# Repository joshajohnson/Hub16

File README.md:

# Hub16

Hub16 is a macropad with a bunch of features you never knew you needed. They include:

- 16 Cherry MX compatible keys, along with switches in each encoder.
- Two rotary encoders, enabling intuitive controls for a wide range of tools including CAD and photo / video editing.
- Inbuilt USB 2.0 Hub with Type-C connectors, allowing connection to other keyboards, memory sticks, wireless receivers and more!
- VIA and QMK compatibility, including a "macro" mode enabling the keys to be dynamically remapped on a host computer.
- 11 addressable RGB LEDs to display state, or just light your desk up.

## Project Status

Project is stable, with assembled boards available at [Tindie](https://www.tindie.com/products/joshajohnson/hub16-programmable-macro-keyboard/).

## Getting Started Guide

- [Keyboard Assembly](Documents/keyboard-assembly.md)
- [VIA Keymap Configuration](Documents/via.md)
- [Macro Configuration](Documents/macro.md)

## Detailed Info

- [Advanced Firmware / Software Configuration](Documents/advanced-config.md)
- [PCB SMT Assembly Guide](Documents/pcba.md)
- [Enclosure Manufacturing](Documents/enclosure.md)

### Repo Contents

- `Documents` contains all documentation and images for the project.
- `Firmware` contains both the source and precompiled binaries for Hub16.
- `Hardware` contains the KiCad design files for the keyboard.
- `josh-kicad-lib` is my personal KiCad parts library which contains many of the parts used.
- `Mechanicals` contain the plate and case design for Hub16.
- `Production` contains all the files required to produce the PCB. It also contains test scripts and jigs.
- `Software` contains all the VIA config, along with template script to use Hub16 as a macropad with software on your computer.

### Notes on the USB Hub

The hub is a four port USB 2.0 Hub with Type-C connectors, aimed at allowing connection of keyboards, mice, memory sticks, wireless receivers, and other small devices (including a second Hub16!)  to your computer.

Due to cost and space constraints, the hub has some limitations. The hub **is not**:

- USB 3.x, Power Delivery, Thunderbolt, DisplayPort, etc compatible.
- Designed to charge your phone quickly. Only 100mA is guaranteed per port.
- Designed to work with power hungry devices such as spinning hard drives.
- Guaranteed to provide full USB 2.0 speeds and performance on all ports.

Might you be able to charge your phone whilst copying files at full speed of a spinning hard drive over a long cable? Maybe. However Hub16 is a macropad first, USB hub second, so if you are looking for a high performance device I'd suggest picking up a dedicated USB hub and just using Hub16 as a macropad.

### Errata

- Boards assembled in 2021 will have an issue with VIA where the LED controls are incorrect. [Follow these instructions to resolve](Documents/via.md#install-via)
- Boards purchased between June 12 and June 22 2020 will not go into the bootloader upon resting from software. Workaround: reset board with physical reset button on bottom of PCB. Fix: reflash the bootloader following [these instructions](Documents/advanced-config.md#Bootloader-Flashing).
- Firmware builds prior to 27th June do not continually send characters when the encoders are depressed.
- Firmware builds prior to 9th June have issues with the bottom right key `p` not functioning correctly.
- Some rotary encoders output flipped signals (clockwise instead of counterclockwise), if after assembly your encoders appear to be sending the wrong signals, comment in line 84 in [config.h](Firmware/hub16/config.h), or alter the setting in your [software](Software).

If you have any questions or comments please get in touch. Asking in the [No Sharp Corners Discord](nosharpcorners.com) Discord or opening an issue / pull request will result in the quickest response.

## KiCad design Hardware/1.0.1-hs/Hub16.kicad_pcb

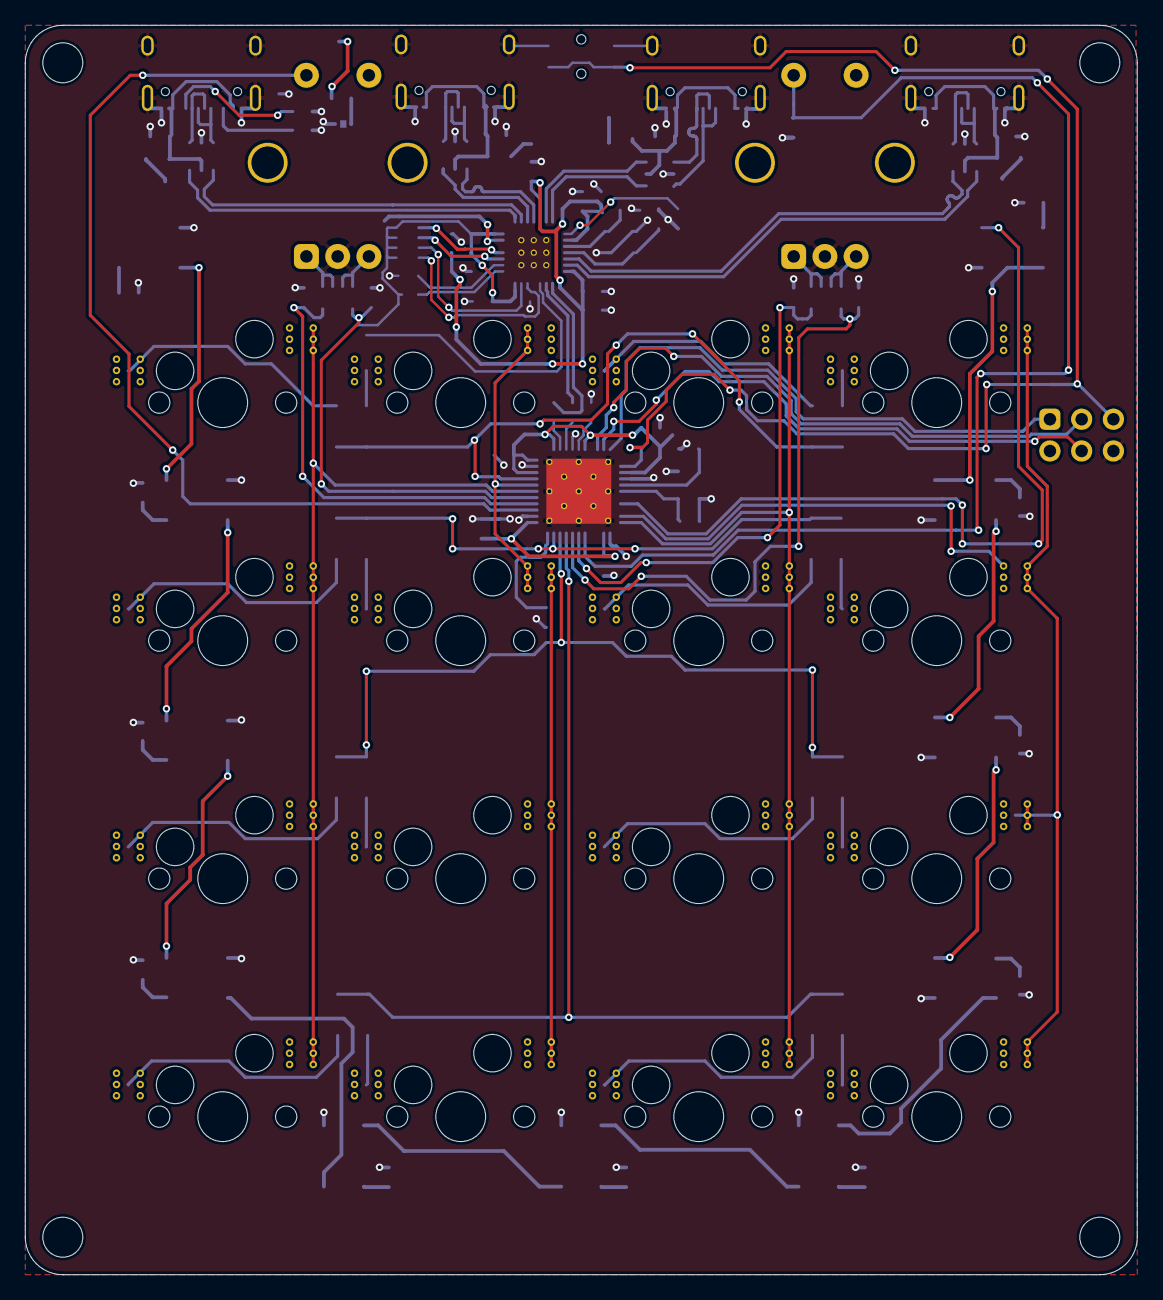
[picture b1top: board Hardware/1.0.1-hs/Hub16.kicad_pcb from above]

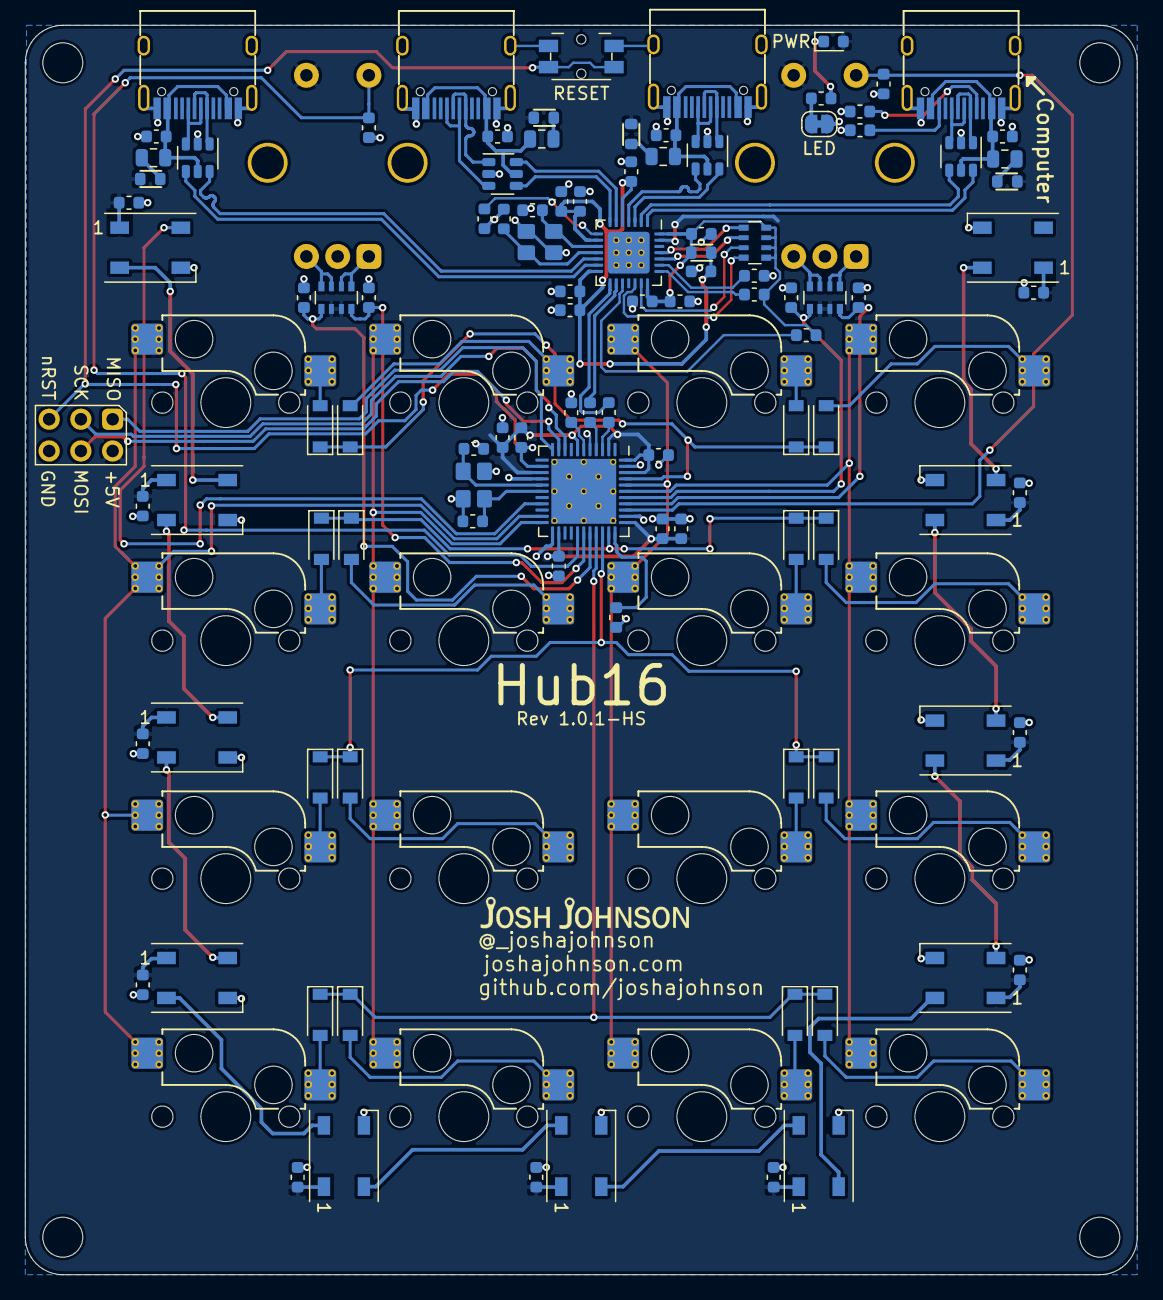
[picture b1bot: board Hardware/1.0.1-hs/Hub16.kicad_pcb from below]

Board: 2 copper layers, 89.0 x 100.0 mm, 132 parts (126 on the bottom side), 99 nets.

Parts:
C1, C12: 10u; C_0603_1608Metric
C2, C3, C17, C18: 15p; C_0603_1608Metric
C4, C5, C19, C20, C22: 1u; C_0603_1608Metric
C6, C7, C8, C9, C10, C11, C13, C14, C15, C16, C21, C23, C24, C25, C26, C27, C28, C29, C30, C31, C32, C33, C34, C35, C36, C37, C38: 100n; C_0603_1608Metric
D1: LED; LED_0603_1608Metric
D2, D3, D4, D10, D16, D22, D23, D29, D30, D31, D32: WS2812B; LED_WS2812B_PLCC4_5.0x5.0mm_P3.2mm
D5, D6, D7, D8, D11, D12, D13, D14, D17, D18, D19, D20, D24, D25, D26, D27: 1N4148; D_SOD-123
F1: 1A; Fuse_0805_2012Metric
F2, F3, F4: 500mA; Fuse_0805_2012Metric
FB1, FB2, FB3, FB4, FB5: 600R; Ferrite_Bead_0603
H1, H2, H3, H4: MH-M3; MountingHole_3.2mm_M3_ISO14580
J1, J3, J4, J5: USB_C_Receptacle_USB2.0; USB_C_U262-161N-4BVC11
J2: AVR-ISP-6; AVR_PROG_2.54_THT
JP11: LED_ON; SolderJumper-2_P1.3mm_Bridged_RoundedPad1.0x1.5mm
K1, K2, K3, K4, K6, K7, K8, K9, K11, K12, K13, K14, K16, K17, K18, K19: Kailh Hotswap Socket; Kailh_Hotswap_1U
LOGO1: Josh-Logo; josh-johnson-logo-17x3
LOGO2: Josh-Details; josh-details
LOGO3: Board-Details; board-title
LOGO4: Logo_Open_Hardware_Small; OSHW-Logo2_9.8x8mm_Mask
R1, R3, R4: 5K1; R_0603_1608Metric
R2, R5, R8, R9, R10, R11, R12: 10K; R_0603_1608Metric
R6, R7: 22R; R_0603_1608Metric
R14: 649R; R_0603_1608Metric
RN1, RN3, RN5: 10K; R_Array_Convex_4x0603
SW1: EVQPUL; Panasonic_EVQPUL_EVQPUC
SW2, SW3: EC11 Encoder; RotaryEncoder_Alps_EC11E-Switch_Vertical_H20mm_CircularMoun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
U1, U4, U5, U6: USBLC6-2SC6; SOT-23-6
U2: ATMEGA32U4; QFN-44-1EP_7x7mm_P0.5mm_EP5.2x5.2mm_ThermalVias
U3: CY7C65632-28LTXCT; QFN-28-1EP_5x5mm_P0.5mm_EP3.35x3.35mm_ThermalVias
Y1: 16MHz; Crystal_SMD_3225-4Pin_3.2x2.5mm
Y2: 12MHz; Crystal_SMD_3225-4Pin_3.2x2.5mm

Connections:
+3.3VA: C13.1, C14.1, C15.1, C16.1, C19.1, C20.1, FB1.1, U3.5, U3.9, U3.14
+3V3: C12.1, C21.1, C22.1, FB1.2, R10.2, R12.2, RN5.5, RN5.6, RN5.7, RN5.8, U3.21, U3.28
+5V: C5.1, C6.2, C7.2, C23.1, C27.1, C28.1, C29.1, C30.1, C31.1, C32.1, C33.1, C34.1, C35.1, C36.1, C37.1, C38.2, D1.2, D2.1, D3.1, D4.1, D10.1, D16.1, D22.1, D23.1, D29.1, D30.1, D31.1, D32.1, FB2.2, FB3.2, FB4.2, FB5.2, J2.2, R2.1, RN1.2, RN1.3, RN3.2, RN3.3, SW2.S1, SW3.S1, U2.2, U2.7, U2.14, U2.24, U2.34, U2.42, U2.44, U3.27
/ENC_1_A: C9.1, RN3.4, U2.37
/ENC_1_B: C8.1, RN3.1, U2.38
/ENC_1_SW: R8.2, SW2.S2, U2.36
/ENC_2_A: C11.1, RN1.4, U2.28
/ENC_2_B: C10.1, RN1.1, U2.29
/ENC_2_SW: R11.2, SW3.S2, U2.27
/LED_1: D22.2, D23.4
/LED_DAT: D2.4, U2.19
/MISO: J2.1, U2.11
/MOSI: J2.4, U2.10
/SCK: J2.3, U2.9
/USB Hub/CON2_D+: J3.A6, J3.B6, U6.3
/USB Hub/CON2_D-: J3.A7, J3.B7, U6.1
/USB Hub/D1_D+: U3.4, U5.4
/USB Hub/D1_D-: U3.3, U5.6
/USB Hub/D2_D+: U3.7, U6.4
/USB Hub/D2_D-: U3.6, U6.6
/USB Hub/D3_D+: U3.13, U4.4
/USB Hub/D3_D-: U3.12, U4.6
/USB Hub/UP_USB_N: U1.6, U3.1
/USB Hub/UP_USB_P: U1.4, U3.2
/USB Hub/USB_DN_D+: R6.2, U3.16
/USB Hub/USB_DN_D-: R7.2, U3.15
/USB Hub/XIN: C17.1, U3.10, Y2.1
/USB Hub/XOUT: C18.1, U3.11, Y2.3
/USB Hub/nOVR_1: RN5.1, U3.25
/USB Hub/nOVR_2: RN5.2, U3.24
/USB Hub/nOVR_3: RN5.3, U3.20
/USB Hub/nOVR_4: RN5.4, U3.19
/USB_UP_D+: J1.A6, J1.B6, U1.3
/USB_UP_D-: J1.A7, J1.B7, U1.1
/col1: K1.1, K2.1, K3.1, K4.1, U2.39
/col2: K6.1, K7.1, K8.1, K9.1, U2.40
/col3: K11.1, K12.1, K13.1, K14.1, U2.22
/col4: K16.1, K17.1, K18.1, K19.1, U2.21
/nRST: J2.5, R2.2, SW1.2, U2.13
/row1: D5.1, D11.1, D17.1, D24.1, U2.41
/row2: D6.1, D12.1, D18.1, D25.1, U2.32
/row3: D7.1, D13.1, D19.1, D26.1, U2.31
/row4: D8.1, D14.1, D20.1, D27.1, U2.30
GND: C1.2, C2.2, C3.2, C4.2, C5.2, C6.1, C7.1, C8.2, C9.2, C10.2, C11.2, C12.2, C13.2, C14.2, C15.2, C16.2, C17.2, C18.2, C19.2, C20.2, C21.2, C22.2, C23.2, C24.2, C25.2, C26.2, C27.2, C28.2, C29.2, C30.2, C31.2, C32.2, C33.2, C34.2, C35.2, C36.2, C37.2, C38.1, D2.3, D3.3, D4.3, D10.3, D16.3, D22.3, D23.3, D29.3, D30.3, D31.3, D32.3, J1.A1, J1.A12, J1.B1, J1.B12, J1.S1, J2.6, J3.A1, J3.A12, J3.B1, J3.B12, J3.S1, J4.A1, J4.A12, J4.B1, J4.B12, J4.S1, J5.A1, J5.A12, J5.B1, J5.B12, J5.S1, JP11.2, R3.1, R4.1, R5.2, R8.1, R9.2, R11.1, R14.2, SW1.1, SW2.C, SW3.C, U1.2, U2.5, U2.15, U2.23, U2.35, U2.43, U2.45, U3.29, U4.2, U5.2, U6.2, Y1.2, Y1.4, Y2.2, Y2.4
unnamed: C2.1, U2.16, Y1.1
unnamed: C3.1, U2.17, Y1.3
unnamed: C4.1, U2.6
unnamed: C24.1, F2.1, J5.A4, J5.A9, J5.B4, J5.B9, U4.5
unnamed: C25.1, F3.1, J4.A4, J4.A9, J4.B4, J4.B9, U5.5
unnamed: C26.1, F4.1, J3.A4, J3.A9, J3.B4, J3.B9, U6.5
unnamed: D1.1, R1.1
unnamed: D2.2, D3.4
unnamed: D3.2, D4.4
unnamed: D5.2, K1.2
unnamed: D6.2, K2.2
unnamed: D7.2, K3.2
unnamed: D8.2, K4.2
unnamed: D10.2, D16.4
unnamed: D4.2, D10.4
unnamed: D11.2, K6.2
unnamed: D12.2, K7.2
unnamed: D13.2, K8.2
unnamed: D14.2, K9.2
unnamed: D16.2, D22.4
unnamed: D17.2, K11.2
unnamed: D18.2, K12.2
unnamed: D19.2, K13.2
unnamed: D20.2, K14.2
unnamed: D23.2, D29.4
unnamed: D24.2, K16.2
unnamed: D25.2, K17.2
unnamed: D26.2, K18.2
unnamed: D27.2, K19.2
unnamed: D29.2, D30.4
unnamed: D30.2, D31.4
unnamed: D31.2, D32.4
unnamed: F1.1, FB5.1
unnamed: F2.2, FB3.1
unnamed: F3.2, FB4.1
unnamed: F4.2, FB2.1
unnamed: J1.A5, R3.2
unnamed: J1.B5, R4.2
unnamed: J4.A6, J4.B6, U5.3
unnamed: J4.A7, J4.B7, U5.1
unnamed: J5.A6, J5.B6, U4.3
unnamed: J5.A7, J5.B7, U4.1
unnamed: JP11.1, R1.2
unnamed: R5.1, U2.33
unnamed: R6.1, U2.4
unnamed: R7.1, U2.3
unnamed: R9.1, U3.23
unnamed: R10.1, U3.17
unnamed: R12.1, U3.22
unnamed: R14.1, U3.8
unnamed: RN1.5, RN1.6, SW3.A
unnamed: RN1.7, RN1.8, SW3.B
unnamed: RN3.5, RN3.6, SW2.A
unnamed: RN3.7, RN3.8, SW2.B
VBUS: C1.1, F1.2, J1.A4, J1.A9, J1.B4, J1.B9, U1.5

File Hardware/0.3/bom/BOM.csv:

Unique ID,Qty,Reference(s),Value,Footprint,Digikey PN,LCSC PN,MPN,Substitute allowed,Notes
Hub16-1,12,"C1, C6, C7, C8, C9, C10, C11, C13, C14, C15, C16, C21",100n,Capacitor_SMD:C_0603_1608Metric,1276-1000-1-ND,,CL10B104KB8NNNC,Y,
Hub16-2,4,"C2, C3, C17, C18",22p,Capacitor_SMD:C_0603_1608Metric,1276-2228-1-ND  ,,CL10C220JB8NFNC ,Y,
Hub16-3,5,"C4, C5, C19, C20, C22",1u,Capacitor_SMD:C_0603_1608Metric,1276-1866-1-ND ,,CL10A105MP8NNNC ,Y,
Hub16-4,1,C12,10u,Capacitor_SMD:C_0603_1608Metric,1276-1871-1-ND ,,CL10A106MP8NNNC ,Y,
Hub16-5,1,D1,LED,LED_SMD:LED_0603_1608Metric,732-4980-1-ND  ,,150060VS75000,Y,
Hub16-6,11,"D2, D3, D4, D10, D16, D22, D23, D29, D30, D31, D32",WS2812B,keyboard:LED_WS2812B_PLCC4_5.0x5.0mm_P3.2mm,1528-1104-ND,C114586,WS2812B,N,LCSC PN - Black Model
Hub16-7,16,"D5, D6, D7, D8, D11, D12, D13, D14, D17, D18, D19, D20, D24, D25, D26, D27",D,Diode_SMD:D_SOD-123,1N4148W-FDICT-ND,C83528,1N4148W-7-F,Y,
Hub16-8,1,F1,500mA,keyboard:Fuse_0805_2012Metric,507-1813-1-ND,C181350,0ZCK0050FF2E,Y,LCSC: Substitute PN
Hub16-9,4,"FB1, FB2, FB3, FB4",600R,josh-passives-smt:Ferrite_Bead_0603,490-1014-1-ND,C19330,BLM18AG601SN1D,Y,
Hub16-10,4,"J1, J3, J4, J5",USB_C_Receptacle_USB2.0,josh-connectors:USB_C_Receptacle_GT-USB-7010,,C319148,U262-161N-4BVC11,N,"Cannot source from Digikey, available on AliExpress: https://www.aliexpress.com/item/33045191307.html"
Hub16-11,1,R1,2K2,Resistor_SMD:R_0603_1608Metric,CR0603-JW-222ELFCT-ND  ,,CR0603-JW-222ELF ,Y,
Hub16-12,5,"R2, R5, R8, R11, R12",10K,Resistor_SMD:R_0603_1608Metric,CR0603-JW-103ELFCT-ND  ,,CR0603-JW-103ELF ,Y,
Hub16-13,2,"R3, R4",5K1,Resistor_SMD:R_0603_1608Metric,118-CR0603-JW-512ELFCT-ND ,,CR0603-JW-512ELF ,Y,
Hub16-14,2,"R6, R7",22R,Resistor_SMD:R_0603_1608Metric,CR0603-JW-220ELFCT-ND  ,,CR0603-JW-220ELF ,Y,
Hub16-15,3,"R9, R10, R13",100K,Resistor_SMD:R_0603_1608Metric,CR0603-JW-104ELFCT-ND ,,CR0603-JW-104ELF ,Y,
Hub16-16,1,R14,649R,Resistor_SMD:R_0603_1608Metric,RHM649CFCT-ND  ,,MCR03ERTF6490 ,Y,
Hub16-17,3,"RN1, RN3, RN5",10K,Resistor_SMD:R_Array_Convex_4x0402,RAVF104DJT10K0CT-ND,,RAVF104DJT10K0,Y,
Hub16-18,1,SW1,SW_Push,josh-buttons-switches:BT_Small_2_Pin,401-1704-1-ND,C354946,KSR223GLFG,Y,LCSC: Substitute PN
Hub16-19,2,"SW2, SW3",Rotary_Encoder_Switch,keyboard:RotaryEncoder_Alps_EC11E-Switch_Vertical_H20mm_CircularMountingHoles,987-1398-ND,C361165,EC11E1834403,Y,Digikey: Substitute PN
Hub16-20,1,U1,TPD2S017,Package_TO_SOT_SMD:SOT-23-6,296-25216-1-ND ,,TPD2S017DBVR,N,"Cannot source from LCSC, no substitutes available "
Hub16-21,1,U2,ATMEGA32U4,Package_QFP:TQFP-44_10x10mm_P0.8mm,ATMEGA32U4-AURCT-ND,C44854,ATMEGA32U4-AU,N,
Hub16-22,1,U3,CY7C65632-28LTXCT,Package_DFN_QFN:QFN-28-1EP_5x5mm_P0.5mm_EP3.35x3.35mm_ThermalVias,428-3156-1-ND,C466886,CY7C65632-28LTXCT,N,
Hub16-23,1,Y1,16MHz,Crystal:Crystal_SMD_3225-4Pin_3.2x2.5mm,535-9134-1-ND ,C179641,ABM8-16.000MHZ-B2-T,Y,
Hub16-24,1,Y2,12MHz,Crystal:Crystal_SMD_3225-4Pin_3.2x2.5mm,535-9826-1-ND,C276421,ABM8-12.000MHZ-B2-T,Y,

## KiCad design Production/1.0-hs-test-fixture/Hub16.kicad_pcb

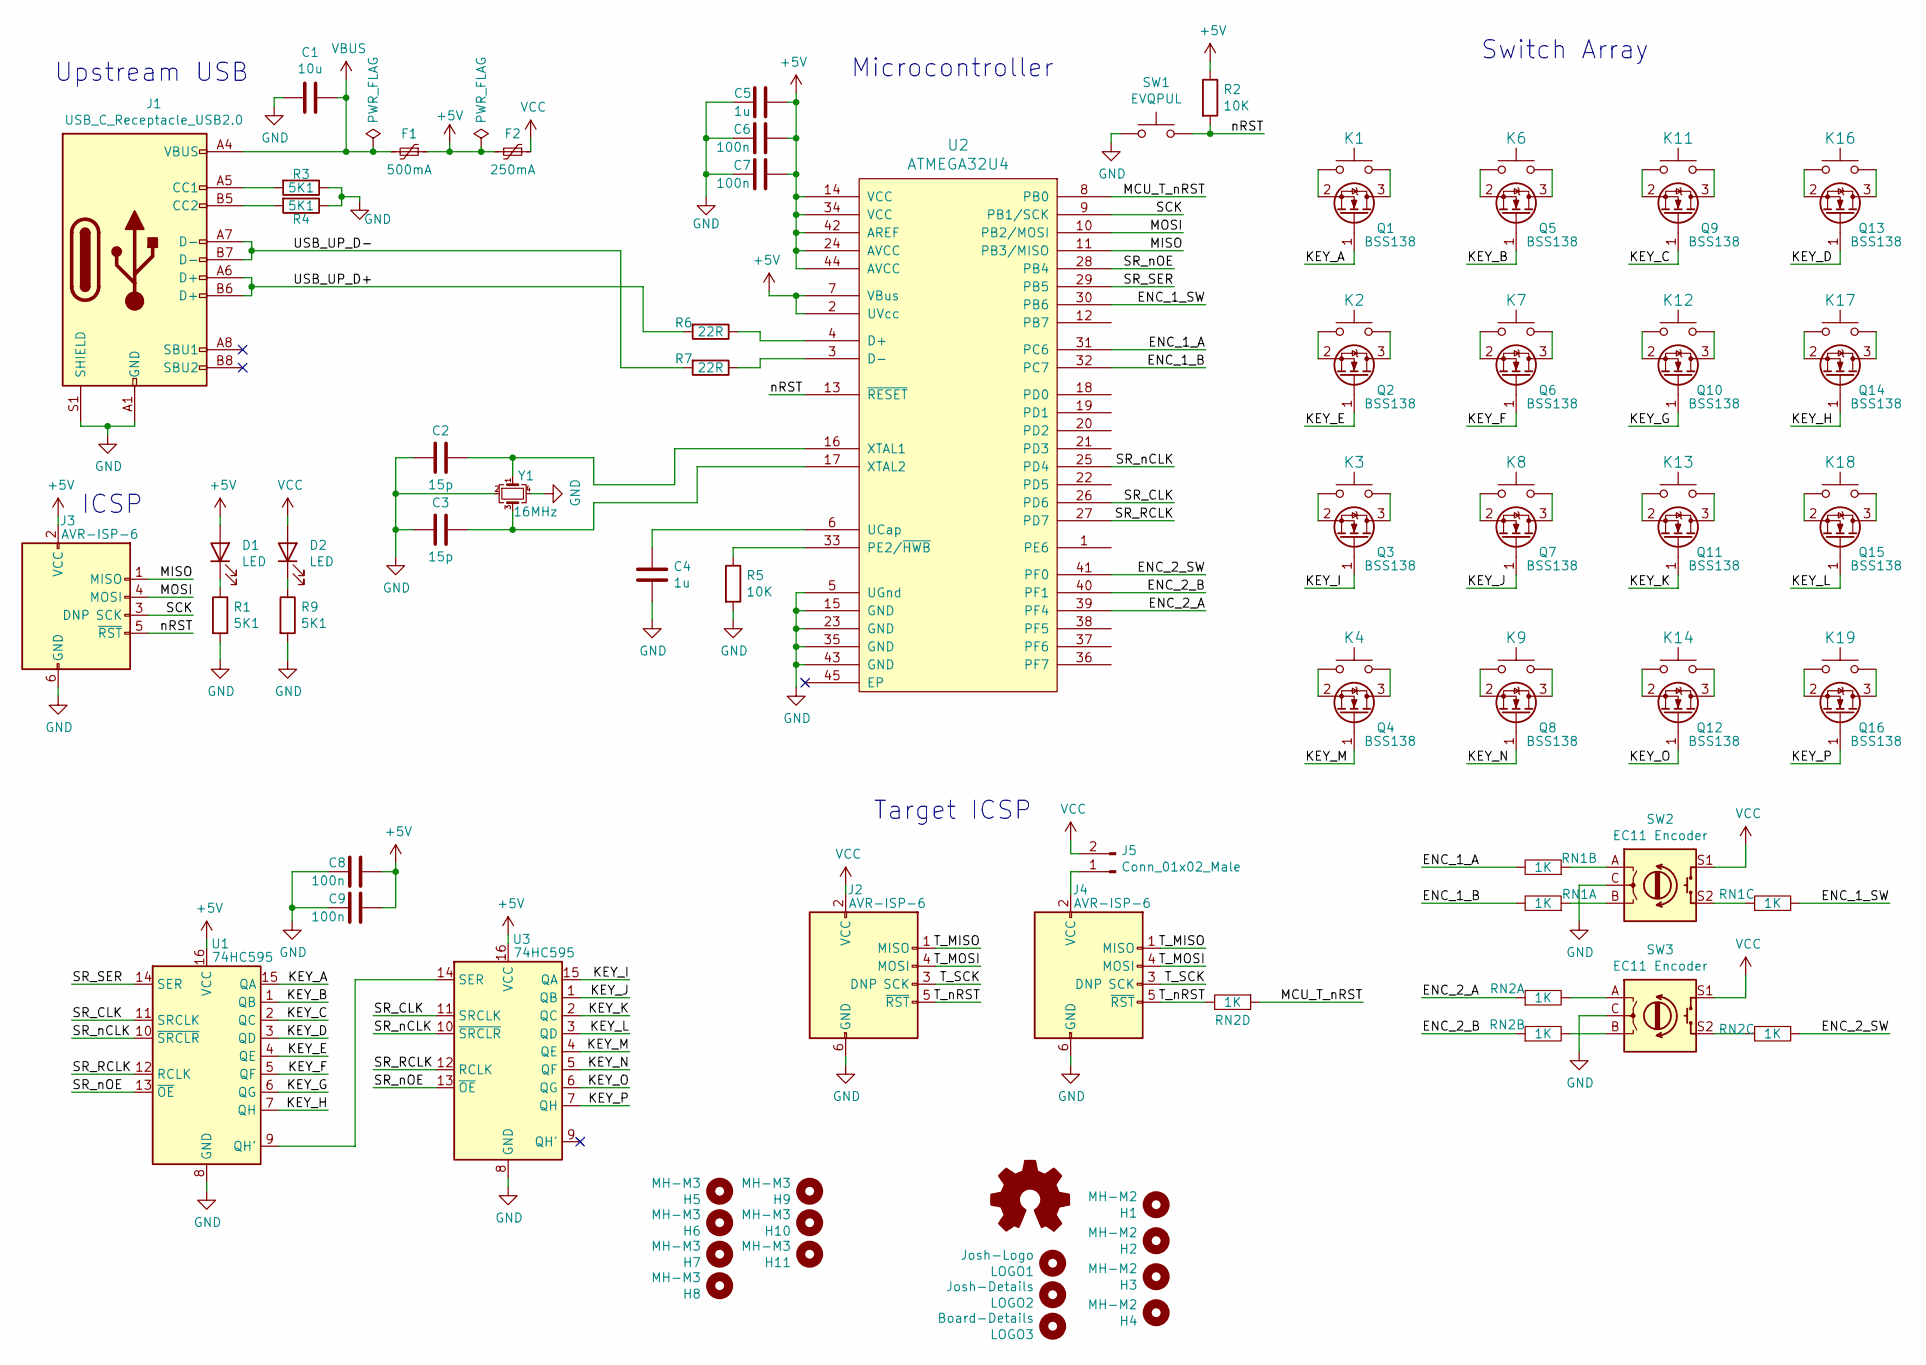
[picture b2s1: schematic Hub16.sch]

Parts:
C1: 10u; C_0603_1608Metric; MPN CL10A106MP8NNNC; DigiKey 1276-1871-1-ND
C2, C3: 15p; C_0603_1608Metric; MPN CL10C150JB8NNNC; DigiKey 1276-1296-2-ND
C4, C5: 1u; C_0603_1608Metric; MPN CL10A105MP8NNNC; DigiKey 1276-1866-1-ND
C6, C7, C8, C9: 100n; C_0603_1608Metric; MPN CL10B104KB8NNNC; DigiKey 1276-1000-1-ND
D1, D2: LED; LED_0603_1608Metric; MPN OSK40603C1E; LCSC C268294
F1: 500mA; Fuse_0805_2012Metric
F2: 250mA; Fuse_0805_2012Metric
H1, H2, H3, H4: MH-M2; MountingHole_2.2mm_M2
H5, H6, H7, H8, H9, H10, H11: MH-M3; MountingHole_3.2mm_M3_Pad
J1: USB_C_Receptacle_USB2.0; USB_C_U262-161N-4BVC11; MPN U262-161N-4BVC11; LCSC C319148
J2: AVR-ISP-6; POGO_P100_AVR_PROG_2.54_THT
J3: AVR-ISP-6; AVR_PROG_2.54_SMT
J4: AVR-ISP-6; IDC-Header_2x03_P2.54mm_Horizontal
J5: Conn_01x02_Male; PinHeader_1x02_P2.54mm_Horizontal
K1, K2, K3, K4, K6, K7, K8, K9, K11, K12, K13, K14, K16, K17, K18, K19: Kailh Hotswap Socket; POGO_P100_Kailh_Hotswap_1U; MPN CPG151101S11
LOGO1: Josh-Logo; josh-johnson-logo-17x3
LOGO2: Josh-Details; josh-details
LOGO3: Board-Details; board-title
LOGO4: Logo_Open_Hardware_Small; OSHW-Logo2_9.8x8mm_Mask
Q1, Q2, Q3, Q4, Q5, Q6, Q7, Q8, Q9, Q10, Q11, Q12, Q13, Q14, Q15, Q16: BSS138; SOT-23
R1, R3, R4, R9: 5K1; R_0603_1608Metric; MPN CR0603-JW-512ELF; DigiKey 118-CR0603-JW-512ELFCT-ND
R2, R5: 10K; R_0603_1608Metric; MPN CR0603-JW-103ELF; DigiKey CR0603-JW-103ELFCT-ND
R6, R7: 22R; R_0603_1608Metric; MPN CR0603-JW-220ELF; DigiKey CR0603-JW-220ELFCT-ND
RN1, RN2: 1K; R_Array_Convex_4x0603
SW1: EVQPUL; Panasonic_EVQPUL_EVQPUC; MPN EVQ-PUL02K; LCSC C397351
SW2, SW3: EC11 Encoder; POGO_P100_RotaryEncoder_Alps_EC11E-Switch_Vertical_H20mm_Ci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; MPN PEC11L-4120F-S0020; DigiKey PEC11L-4120F-S0020-ND
U1, U3: 74HC595; SOIC-16_3.9x9.9mm_P1.27mm
U2: ATMEGA32U4; TQFP-44_10x10mm_P0.8mm; MPN ATMEGA32U4-MU; LCSC C45874
Y1: 16MHz; Crystal_SMD_3225-4Pin_3.2x2.5mm; MPN ABM8-16.000MHZ-10-1-U-T; LCSC C164044

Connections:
+5V: C5.1, C6.2, C7.2, C8.2, C9.2, D1.2 (A), F1.1, F2.2, J3.2 (VCC), R2.1, U1.16 (VCC), U2.2 (UVcc), U2.7 (VBus), U2.14 (VCC), U2.24 (AVCC), U2.34 (VCC), U2.42 (AREF), U2.44 (AVCC), U3.16 (VCC)
/ENC_1_A: RN1.6, U2.31 (PC6)
/ENC_1_B: RN1.5, U2.32 (PC7)
/ENC_1_SW: RN1.7, U2.30 (PB6)
/ENC_2_A: RN2.4, U2.39 (PF4)
/ENC_2_B: RN2.3, U2.40 (PF1)
/ENC_2_SW: RN2.2, U2.41 (PF0)
/KEY_A: Q1.1 (G), U1.15 (QA)
/KEY_B: Q5.1 (G), U1.1 (QB)
/KEY_C: Q9.1 (G), U1.2 (QC)
/KEY_D: Q13.1 (G), U1.3 (QD)
/KEY_E: Q2.1 (G), U1.4 (QE)
/KEY_F: Q6.1 (G), U1.5 (QF)
/KEY_G: Q10.1 (G), U1.6 (QG)
/KEY_H: Q14.1 (G), U1.7 (QH)
/KEY_I: Q3.1 (G), U3.15 (QA)
/KEY_J: Q7.1 (G), U3.1 (QB)
/KEY_K: Q11.1 (G), U3.2 (QC)
/KEY_L: Q15.1 (G), U3.3 (QD)
/KEY_M: Q4.1 (G), U3.4 (QE)
/KEY_N: Q8.1 (G), U3.5 (QF)
/KEY_O: Q12.1 (G), U3.6 (QG)
/KEY_P: Q16.1 (G), U3.7 (QH)
/MCU_T_nRST: RN2.1, U2.8 (PB0)
/MISO: J3.1 (MISO), U2.11 (PB3/MISO)
/MOSI: J3.4 (MOSI), U2.10 (PB2/MOSI)
/SCK: J3.3 (SCK), U2.9 (PB1/SCK)
/SR_CLK: U1.11 (SRCLK), U2.26 (PD6), U3.11 (SRCLK)
/SR_RCLK: U1.12 (RCLK), U2.27 (PD7), U3.12 (RCLK)
/SR_SER: U1.14 (SER), U2.29 (PB5)
/SR_nCLK: U1.10 (~SRCLR), U2.25 (PD4), U3.10 (~SRCLR)
/SR_nOE: U1.13 (~OE), U2.28 (PB4), U3.13 (~OE)
/T_MISO: J2.1 (MISO), J4.1 (MISO)
/T_MOSI: J2.4 (MOSI), J4.4 (MOSI)
/T_SCK: J2.3 (SCK), J4.3 (SCK)
/T_nRST: J2.5 (~RST), J4.5 (~RST), RN2.8
/USB_UP_D+: J1.A6 (D+), J1.B6 (D+), R6.2
/USB_UP_D-: J1.A7 (D-), J1.B7 (D-), R7.2
/nRST: J3.5 (~RST), R2.2, SW1.2, U2.13 (~RESET)
GND: C1.2, C2.2, C3.2, C4.2, C5.2, C6.1, C7.1, C8.1, C9.1, J1.A1 (GND), J1.A12 (GND), J1.B1 (GND), J1.B12 (GND), J1.S1 (SHIELD), J2.6 (GND), J3.6 (GND), J4.6 (GND), R1.2, R3.1, R4.1, R5.2, R9.2, SW1.1, SW2.C, SW3.C, U1.8 (GND), U2.5 (UGnd), U2.15 (GND), U2.23 (GND), U2.35 (GND), U2.43 (GND), U3.8 (GND), Y1.2, Y1.4
unnamed: C2.1, U2.16 (XTAL1), Y1.1
unnamed: C3.1, U2.17 (XTAL2), Y1.3
unnamed: C4.1, U2.6 (UCap)
unnamed: D1.1 (K), R1.1
unnamed: D2.1 (K), R9.1
unnamed: J1.A5 (CC1), R3.2
unnamed: J1.B5 (CC2), R4.2
unnamed: J4.2 (VCC), J5.1
unnamed: K1.1, Q1.3 (D)
unnamed: K1.2, Q1.2 (S)
unnamed: K2.1, Q2.3 (D)
unnamed: K2.2, Q2.2 (S)
unnamed: K3.1, Q3.3 (D)
unnamed: K3.2, Q3.2 (S)
unnamed: K4.1, Q4.3 (D)
unnamed: K4.2, Q4.2 (S)
unnamed: K6.1, Q5.3 (D)
unnamed: K6.2, Q5.2 (S)
unnamed: K7.1, Q6.3 (D)
unnamed: K7.2, Q6.2 (S)
unnamed: K8.1, Q7.3 (D)
unnamed: K8.2, Q7.2 (S)
unnamed: K9.1, Q8.3 (D)
unnamed: K9.2, Q8.2 (S)
unnamed: K11.1, Q9.3 (D)
unnamed: K11.2, Q9.2 (S)
unnamed: K12.1, Q10.3 (D)
unnamed: K12.2, Q10.2 (S)
unnamed: K13.1, Q11.3 (D)
unnamed: K13.2, Q11.2 (S)
unnamed: K14.1, Q12.3 (D)
unnamed: K14.2, Q12.2 (S)
unnamed: K16.1, Q13.3 (D)
unnamed: K16.2, Q13.2 (S)
unnamed: K17.1, Q14.3 (D)
unnamed: K17.2, Q14.2 (S)
unnamed: K18.1, Q15.3 (D)
unnamed: K18.2, Q15.2 (S)
unnamed: K19.1, Q16.3 (D)
unnamed: K19.2, Q16.2 (S)
unnamed: R5.1, U2.33 (PE2/~HWB)
unnamed: R6.1, U2.4 (D+)
unnamed: R7.1, U2.3 (D-)
unnamed: RN1.2, SW2.S2
unnamed: RN1.3, SW2.A
unnamed: RN1.4, SW2.B
unnamed: RN2.5, SW3.A
unnamed: RN2.6, SW3.B
unnamed: RN2.7, SW3.S2
unnamed: U1.9 (QH'), U3.14 (SER)
VBUS: C1.1, F1.2, J1.A4 (VBUS), J1.A9 (VBUS), J1.B4 (VBUS), J1.B9 (VBUS)
VCC: D2.2 (A), F2.1, J2.2 (VCC), J5.2, SW2.S1, SW3.S1

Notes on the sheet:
Switch Array
Microcontroller
Upstream USB
ICSP
Target ICSP

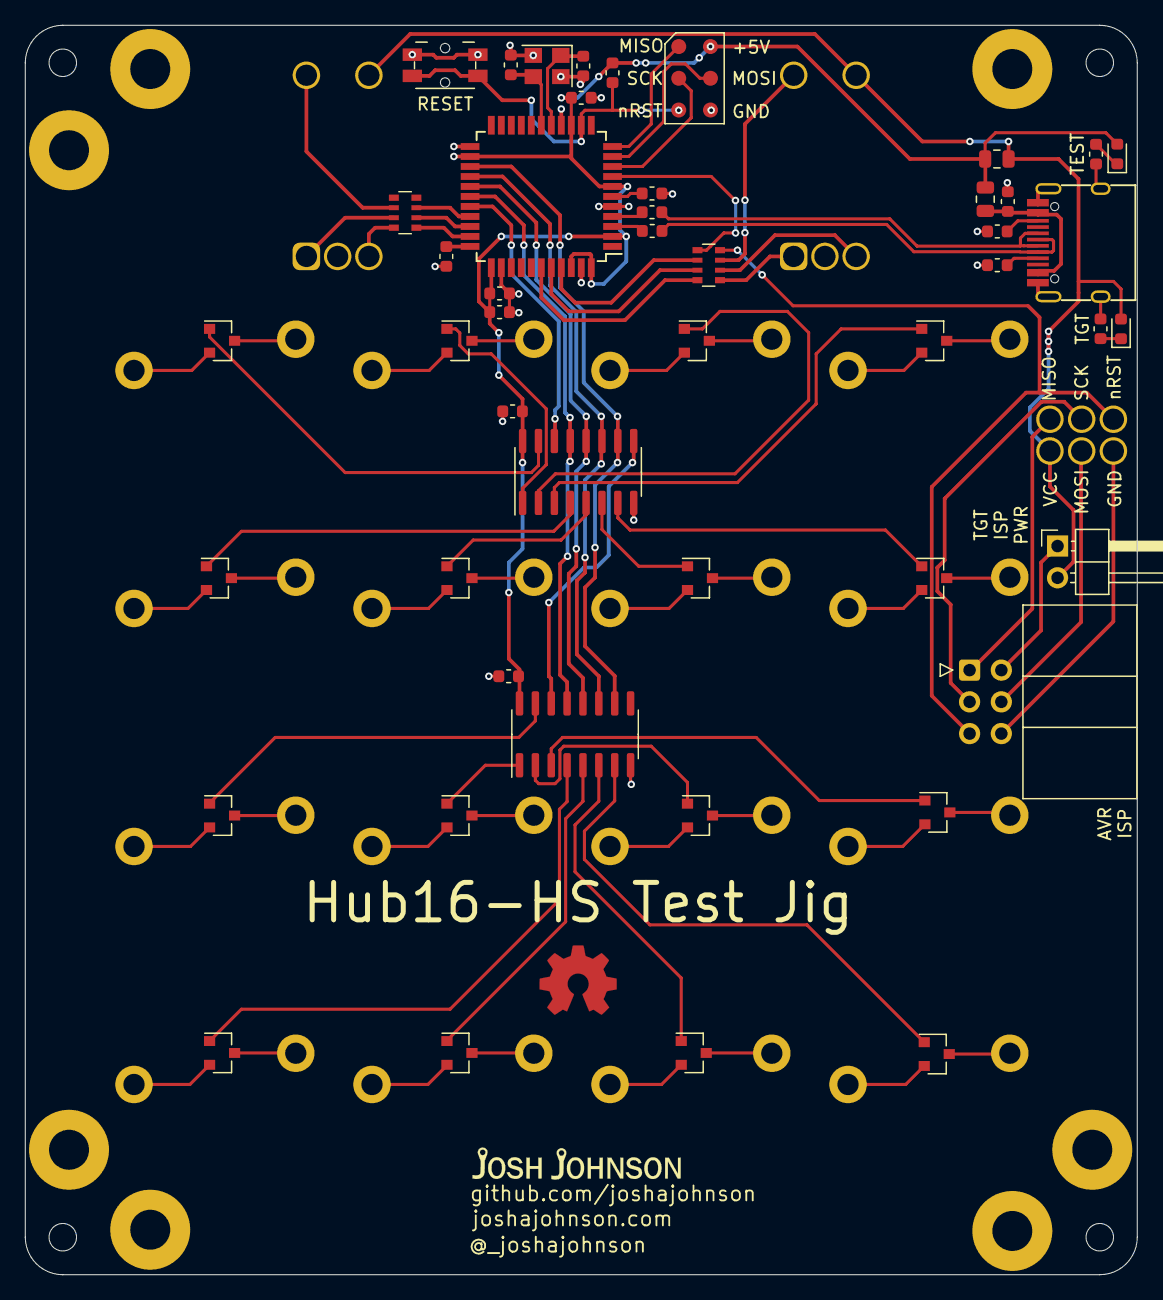
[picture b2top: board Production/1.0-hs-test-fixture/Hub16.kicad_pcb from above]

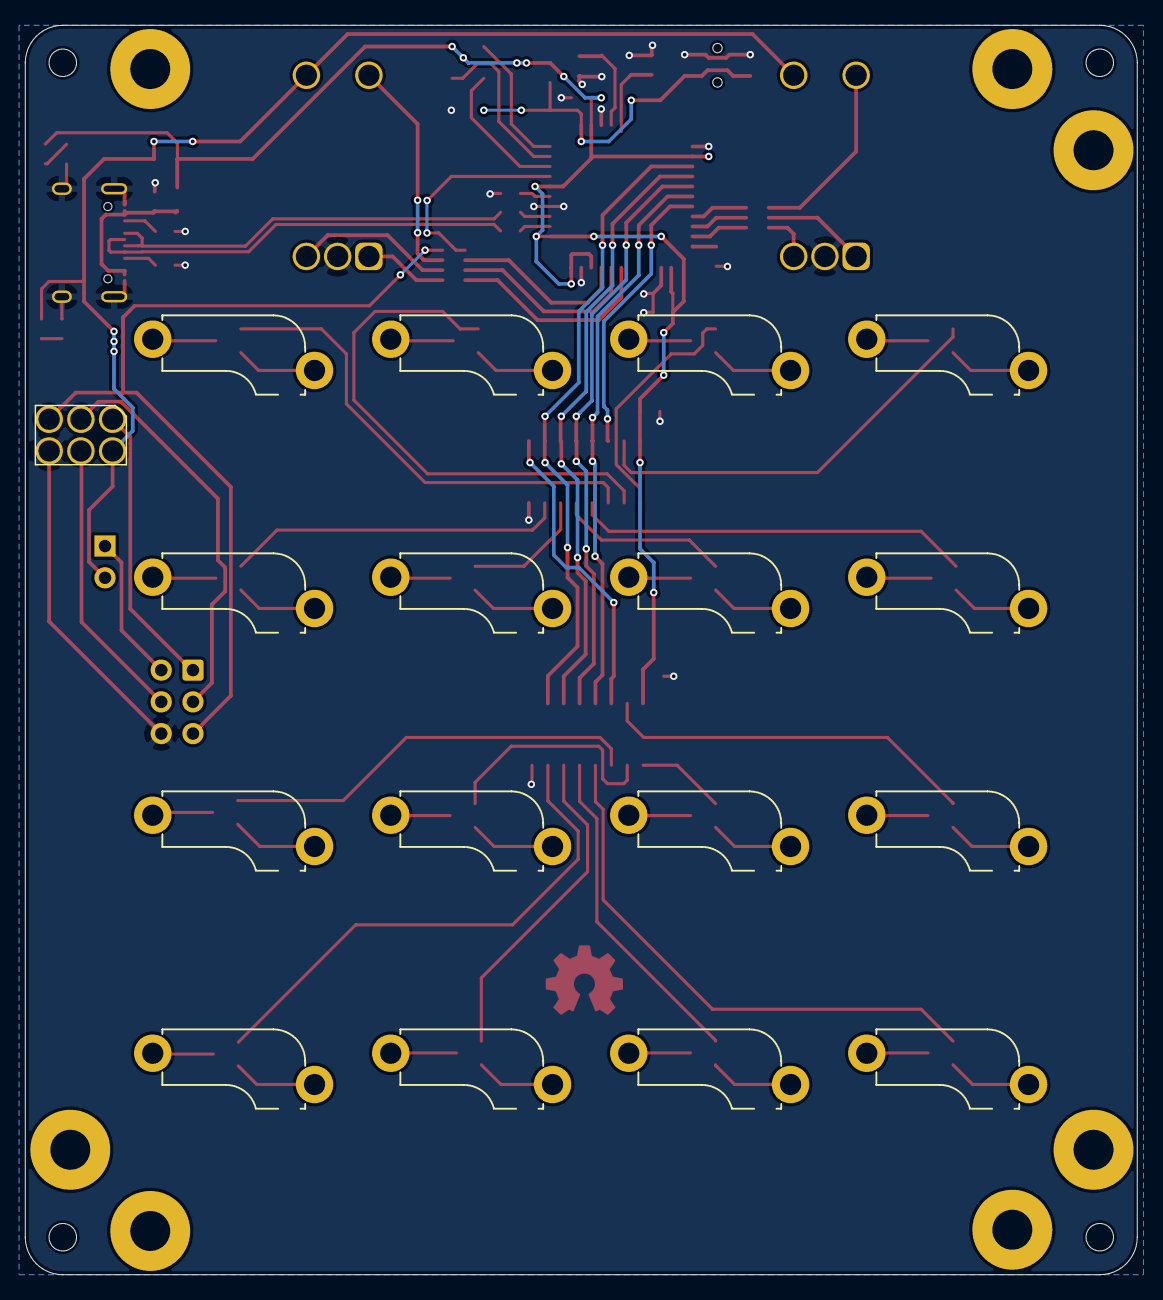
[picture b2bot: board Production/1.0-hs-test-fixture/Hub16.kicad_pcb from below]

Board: 2 copper layers, 89.0 x 100.0 mm, 83 parts (18 on the bottom side), 92 nets.

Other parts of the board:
LOGO4#2: Logo_Open_Hardware_Small; OSHW-Logo2_9.8x8mm_Mask

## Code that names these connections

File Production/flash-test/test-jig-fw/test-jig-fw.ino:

// 74HC595 Pins
#define SR_nOE  8   // B4
#define SR_SER  9   // B5
#define SR_CLK  12  // D6
#define SR_RCLK 6   // D7
#define SR_nCLR 4   // D4

// Encoder Pins
#define ENC_1_SW  10  // B6
#define ENC_2_SW  A5  // F0

#define ENC_1_A   5   // C6
#define ENC_1_B   13  // C7

#define ENC_2_A   A3  // F4
#define ENC_2_B   A4  // F1

#define CLOCKWISE 1
#define ANTICLOCK 2

#define ENC_1     1
#define ENC_2     2

// DUT RST
#define DUT_nRST    PB0
#define DUT_nRST_P  PORTB

// Commands
#define ENTER       64
#define HIGH_Z      128
#define SOFT_RESET  254
#define HARD_RESET  255

// Non Arduino Pin IO
#define dirOut(port,pin) 	  (*(&port-1)) |= (1<<(pin))
#define dirIn(port,pin) 	  (*(&port-1)) &= ~(1<<(pin))
#define clearBit(port,pin) 	(port) &= ~(1<<(pin))
#define setBit(port,pin) 	  (port) |= (1<<(pin))

void press_key(uint8_t key);
void press_enter(void);
void shift_out(uint16_t bitstream);
void rotate_encoder(uint8_t encoder, uint8_t dir);

void setup() 
{
  // Shift Reg
  pinMode(SR_nOE, OUTPUT);
  pinMode(SR_SER, OUTPUT);
  pinMode(SR_nCLR, OUTPUT);
  pinMode(SR_CLK, OUTPUT);
  pinMode(SR_RCLK, OUTPUT);

  // Encoders
  pinMode(ENC_1_SW, OUTPUT);
  pinMode(ENC_2_SW, OUTPUT);
  pinMode(ENC_1_A, OUTPUT);
  pinMode(ENC_1_B, OUTPUT);
  pinMode(ENC_2_A, OUTPUT);
  pinMode(ENC_2_B, OUTPUT);

  digitalWrite(ENC_1_SW, LOW);
  digitalWrite(ENC_2_SW, LOW);
  digitalWrite(ENC_1_A, HIGH);
  digitalWrite(ENC_1_B, HIGH);
  digitalWrite(ENC_2_A, HIGH);
  digitalWrite(ENC_2_B, HIGH);

  // DUT Reset
  dirIn(DUT_nRST_P, DUT_nRST);

  // SR should be high Z
  digitalWrite(SR_nOE, HIGH);
  digitalWrite(SR_nCLR, HIGH);

  // Serial
  Serial.begin(115200);
}

void loop() 
{
  while (Serial.available() > 0)
  {
    uint8_t data = Serial.parseInt();

    if (data >= 1 && data <= 16) // A = 1, P = 16
    {
      if (data == 16)  // If P, we need to wait for tap dance to clear after pressing alpha
      {
        delay(500);
      }
      press_key(data);
      delay(500);
      if (data == 16)  // If P, we need to wait for tap dance to clear after pressing alpha
      {
        delay(500);
      }
      press_enter();
    }
    else if (data > 16 && data <= 22) // Q = 17, V = 22
    {

      if (data == 17)
      {
        Serial.println("Encoder 1, Clockwise");
        rotate_encoder(ENC_1, CLOCKWISE);
        press_enter();
      }
      else if (data == 18)
      {
        Serial.println("Encoder 1, Anticlock");
        rotate_encoder(ENC_1, ANTICLOCK);
        press_enter();
      }
      else if (data == 19)
      {
        Serial.println("Encoder 1, Button");
        digitalWrite(ENC_1_SW, HIGH);
        delay(50);
        digitalWrite(ENC_1_SW, LOW);
        press_enter();
      }
      else if (data == 20)
      {
        Serial.println("Encoder 2, Clockwise");
        rotate_encoder(ENC_2, CLOCKWISE);
        press_enter();
      }
      else if (data == 21)
      {
        Serial.println("Encoder 2, Anticlock");
        rotate_encoder(ENC_2, ANTICLOCK);
        press_enter();
      }
      else if (data == 22)
      {
        Serial.println("Encoder 2, Button");
        digitalWrite(ENC_2_SW, HIGH);
        delay(50);
        digitalWrite(ENC_2_SW, LOW);
        press_enter();
      }
    }
    else if (data == ENTER)
    {
      press_enter();
    }
    else if (data == 128) // High Z all the things
    {
      digitalWrite(SR_nOE, HIGH);
      dirIn(DUT_nRST_P, DUT_nRST);
      Serial.println("High Z IO");
    }
    else if (data == SOFT_RESET)
    {
      Serial.println("Soft Reset");
      press_key(15);
      delay(50);
      press_key(15);
      
    }
    else if (data == HARD_RESET)
    {
      Serial.println("Hard Reset");
      dirOut(DUT_nRST_P, DUT_nRST);
      clearBit(DUT_nRST_P, DUT_nRST);
      delay(50);
      setBit(DUT_nRST_P, DUT_nRST);
      dirIn(DUT_nRST_P, DUT_nRST);
    }
  }
}

// Double taps "P" to hit enter
void press_enter(void)
{
  press_key(16);
  delay(50);
  press_key(16);
}

// Presses the given key, with A = 1, P = 16
void press_key(uint8_t key)
{
  Serial.print("Pressing Key: ");
  Serial.println(key, DEC);

  // digitalWrite(SR_nOE, HIGH);
  digitalWrite(SR_nOE, LOW);
  shift_out(1 << (key - 1)); // Convert from A=1 to A=0
  delay(100);
  shift_out(0b0000000000000000); // Clear
}

// Sets keys per input bitstream
void shift_out(uint16_t bitstream)
{
  digitalWrite(SR_RCLK, LOW);
  shiftOut(SR_SER, SR_CLK, MSBFIRST, (bitstream & 0xFF00) >> 8); // second byte
  shiftOut(SR_SER, SR_CLK, MSBFIRST, (bitstream & 0xFF));        // first byte
  digitalWrite(SR_RCLK, HIGH);
}

void rotate_encoder(uint8_t encoder, uint8_t dir)
{

  if (encoder == ENC_1 && dir == CLOCKWISE)
  {
    digitalWrite(ENC_1_B, LOW);
    delay(10);
    digitalWrite(ENC_1_A, LOW);
    delay(10);
    digitalWrite(ENC_1_B, HIGH);
    delay(10);
    digitalWrite(ENC_1_A, HIGH);
    delay(100);
  }
  else if (encoder == ENC_1 && dir == ANTICLOCK)
  {
    digitalWrite(ENC_1_A, LOW);
    delay(10);
    digitalWrite(ENC_1_B, LOW);
    delay(10);
    digitalWrite(ENC_1_A, HIGH);
    delay(10);
    digitalWrite(ENC_1_B, HIGH);
    delay(100);
  }
  else if (encoder == ENC_2 && dir == CLOCKWISE)
  {
    digitalWrite(ENC_2_B, LOW);
    delay(10);
    digitalWrite(ENC_2_A, LOW);
    delay(10);
    digitalWrite(ENC_2_B, HIGH);
    delay(10);
    digitalWrite(ENC_2_A, HIGH);
    delay(100);
  }
  else if (encoder == ENC_2 && dir == ANTICLOCK)
  {
    digitalWrite(ENC_2_A, LOW);
    delay(10);
    digitalWrite(ENC_2_B, LOW);
    delay(10);
    digitalWrite(ENC_2_A, HIGH);
    delay(10);
    digitalWrite(ENC_2_B, HIGH);
    delay(100);
  }
}

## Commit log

2020-01-03 add gitignore
2020-01-03 starting afresh
2020-01-03 changing sw15/16 code
2020-01-03 update pnp tool
2020-01-03 update documentation
2020-01-05 more progress
2020-01-06 removed encoder bodge and revd documentation
2020-01-25 add a few more things to check
2020-01-25 add notes regarding K19
2020-02-09 add images and start assembly instructions
2020-02-09 add assembly instructions
2020-02-09 update docs
2020-02-15 now available for sale!
2020-02-15 fixed errata
2020-02-23 r0.4 and hunting down bugs
2020-02-23 fix p issue
2020-02-28 update code refrences
2020-03-07 update kicad lib
2020-03-07 fix submodule url issue
2020-03-07 back to ssh
2020-03-22 Fix path to hub16.ahk
2020-03-22 Add macOS instructions
2020-03-22 Change section name
2020-03-25 Add complex rule template note for macOS/karabiner
2020-03-28 macos: Add karabiner config
2020-03-28 macos: Update with KE config file
2020-03-30 release r0.5
2020-04-17 change to install instructions
2020-05-30 updated documentation + wrote test script
2020-05-30 correct RN part numbers + generate pdf of schematic
2020-06-02 update case specs + programming script
2020-06-02 changes during flashing first units
2020-06-06 update keyboard diagram + programming script improvement
2020-06-10 add repeat option to script
2020-06-15 add test comments + script
2020-06-23 update assembly instructions
2020-06-27 fix hwbe fuse not being set
2020-06-27 updating firmware documentation
2020-06-27 update example ahk script
2020-07-02 update firmware
2020-07-07 change vid:pid
2020-07-10 improve debounce code
2020-07-15 increase robustness
2020-07-15 more layout
2020-07-21 use bottom paste instead of top...
2020-07-24 Remove device entries unrelated to Hub16
2020-07-24 Remove default config that Karabiner automatically adds when 'Use f keys as standard function keys' is checked
2020-07-24 Use the same rotary encoder bindings on windows and mac
2020-07-26 add power led disable instructions
2020-07-26 update karabiner configs due to VID:PID changes
2020-08-08 update gitignore
2020-08-12 clean up routing, should probably start USB hub from scratch...
2020-08-12 laid out USB hub from scratch, much better
2020-08-12 probably zoomed out?
2020-08-13 robustness ++
2020-08-15 update link
2020-08-15 render not working on github
2020-08-15 update extension to caps
2020-08-16 0.6 hs laid out, USB cleanup + PDN checks TODO
2020-08-16 0.6-hs is now 0.7-hs
2020-08-17 clean up usb routing + pdn check
2020-08-19 update board
2020-08-19 add non hotswap version
2020-08-20 update software operation with mac f24 usage
2020-08-20 add bottom fr4 plate
2020-08-22 fix v0.5 bom + release prototypes
2020-08-22 update sockets with courtyard
2020-08-22 update footprints + bom
2020-08-22 fix broken image link to led_cut.JPG
2020-08-25 add note on uncommenting out code
2020-09-04 text changes
2020-09-06 move res with HS interference
2020-09-09 update fuse values
2020-09-14 add v1.0 files
2020-09-20 move mechanicals + update producting flash script
2020-10-10 update test script + enclosure files
2020-10-11 documentation updates
2020-10-16 update bootloader link
2020-11-14 update assembly instructions + readme edits
2020-11-14 update images to latest revision
2020-11-21 initial test fixture layout done
2020-11-29 update bare-bones spelling + text fixture update
2020-12-12 test fixture for keys working
2020-12-13 all but encoder working
2021-01-05 Note states left key but * is on the right
    I believe the instructions should say "bottom right" instead of "bottom left"
2021-01-17 update firmware files
2021-03-08 add fix for via keycode difference
2021-03-08 link to header
2021-03-08 bump avrdude
2021-03-08 add link to encoder video
2021-03-21 1.0.1 initial commit
2021-06-20 remove test jig, update assembly
2021-06-26 clean up production files
